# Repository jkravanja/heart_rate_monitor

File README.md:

# heart_rate_monitor
Heart rate monitor designed in KiCad, using Nordic Semiconductor NRF51822 bluetooth module and TI AFE4400 heart rate module.

The repository contains a KiCad design of a 5x5 cm heart rate monitor breakout board. Some libraries were borrowed from Guan Yang's github projects (https://github.com/guanix/boards). Also, some design aspects of the circuit were inspired by HackManhattan Nordic nrf51822 beakout board (http://dangerousprototypes.com/2013/05/19/hackmanhattans-nordic-nrf51822-breakout-board/)

[Schematics](https://github.com/jkravanja/heart_rate_monitor/blob/master/hr.pdf)

In addition to AFE440 for heart rate measurements and NRF51822 for BLE communications, the circuit also contains a [Freescale MMA8452 3-axis accelerometer](http://www.nxp.com/files/sensors/doc/data_sheet/MMA8452Q.pdf), CAT24M01 1Mb EEPROM and an additional heart rate circuit composed of just a few simple elements (see bottom center of the schematics). The circuit was inspired by [this article](http://www.biofotonika.lu.lv/fileadmin/user_upload/lu_portal/projekti/biofotonika/Publikacijas/A4/SPIE/22.Kviesis-A_photoplethysmography_device_for_multipurpose_blood_circulatory_system_assessment.pdf) and presents a cheaper and simpler option to AFE4400.

Image of manufactured PCB

Components were soldered with reflow technique. Some joints had to be manually corrected using soldering iron

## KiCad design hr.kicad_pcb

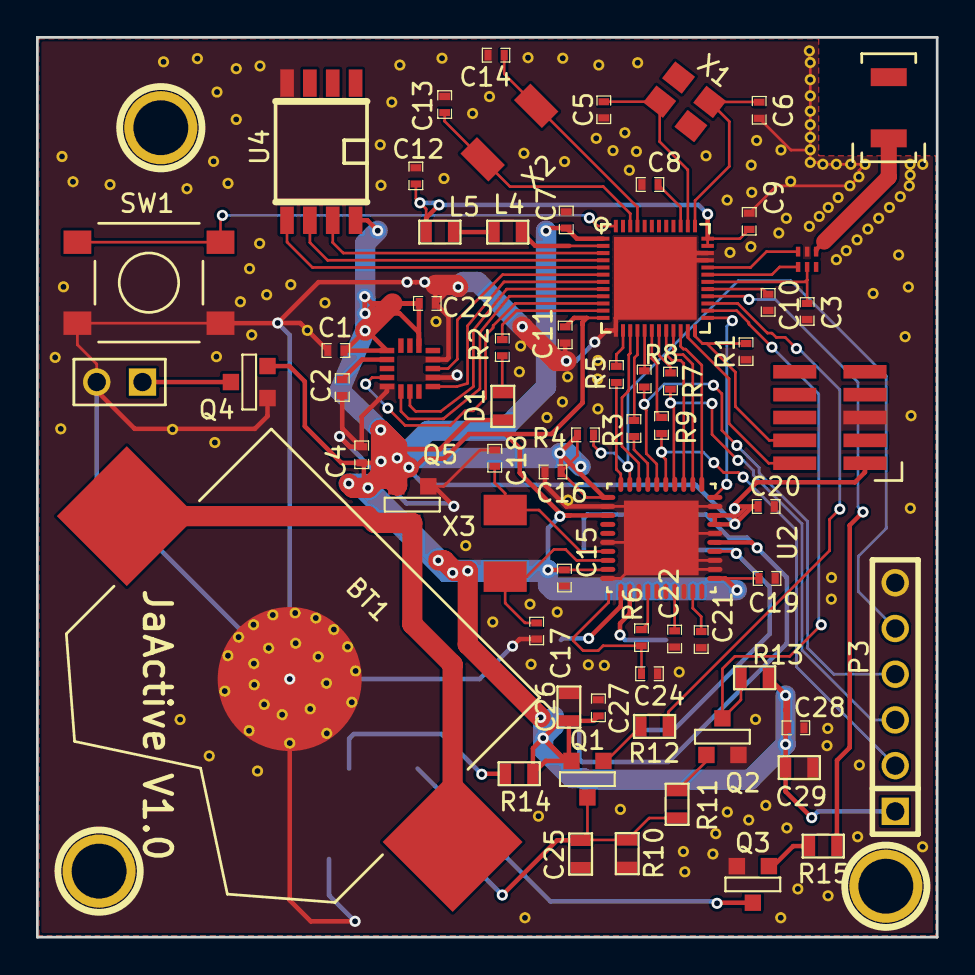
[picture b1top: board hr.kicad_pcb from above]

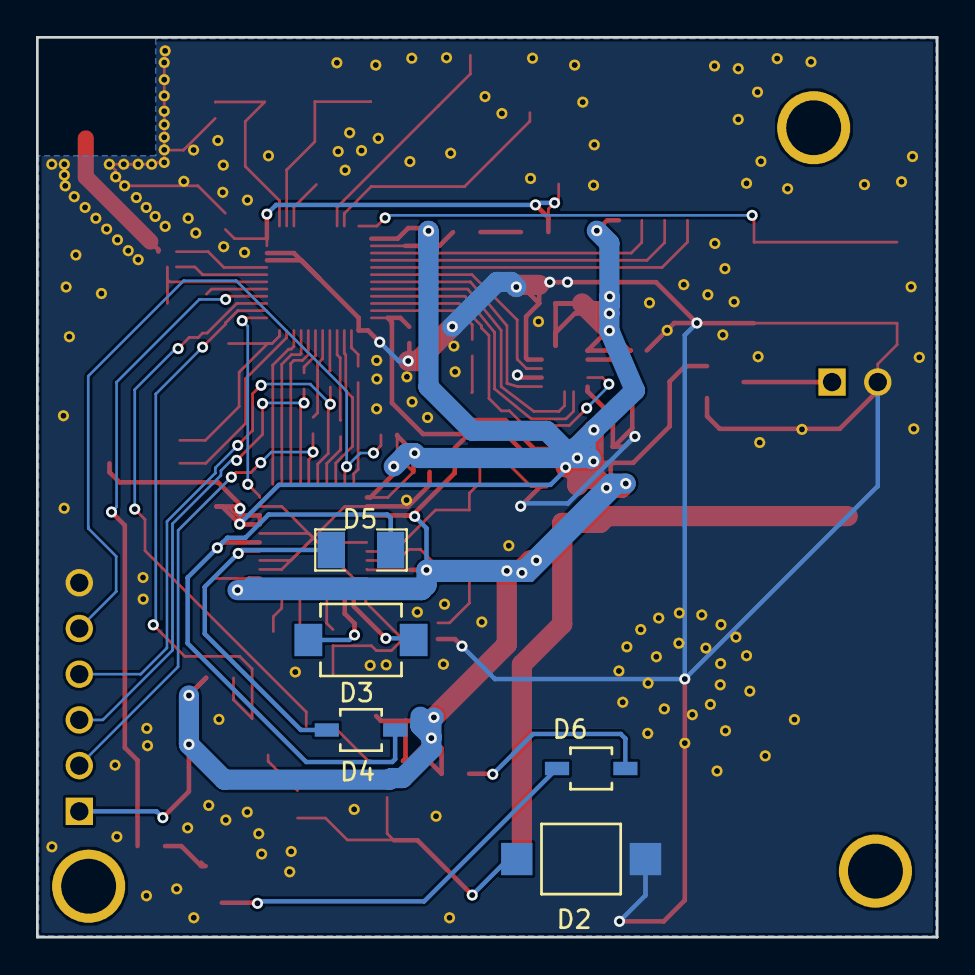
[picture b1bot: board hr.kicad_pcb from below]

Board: 2 copper layers, 50.0 x 50.0 mm, 74 parts (5 on the bottom side), 66 nets.

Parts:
1PIN, 1PIN#2, 1PIN#3: P***; 1pin
B1: Balun Johanson 2450BM14A0002; BALUNJOHANSON-2450BM14A0002
BT1: BATTERY; BatteryHolderCR2032
C1, C2, C16: 0.1 uF; SM0402
C3: 2.2nF; SM0402
C4, C7: 4.7uF; SM0402
C5, C6, C13, C14: 20pF; SM0402
C8, C11, C15, C19: 0.1uF; SM0402
C9: 1nF; SM0402
C10: 47nF; SM0402
C12, C20: 1uF; SM0402
C17, C18: 33p; SM0402
C21, C22: 2.2uF; SM0402
C23: 4.7 uF; SM0402
C24: 0.01 uF; SM0402
C25, C29: 1 nF; SM0603
C26: 220 nF; SM0603
C27, C28: 1 uF; SM0402
D1: LED; SM0603
D2: PHOTODIODE; VBPW34FA
D3: PHOTODIODE; QSB34_Photodiode
D4: IR; VSBM2943
D5: RED; SM1206
D6: LED; VSBM2943
IC1: NRF51822; QFN48+1-0.4MM-SHORTPADS
L4: 10uH; SM0603
L5: 15nH; SM0603
P1: CONN_5X2; PIN-5x2-50MIL
P2: CONN_2; PIN_ARRAY_2X1
P3: CONN_3X2; PIN_ARRAY-6X1
Q1, Q4, Q5: MOSFET_P; SOT23GDS
Q2, Q3: MOSFET_N; SOT23GDS
R1: 12K; SM0402
R2: 100R; SM0402
R3, R7, R8, R9: 4.7k; SM0402
R4: 10k; SM0402
R5: 10; SM0402
R6: 1k; SM0402
R10: 1 M; SM0603
R11, R12: 100 k; SM0603
R13: 3 k; SM0603
R14, R15: R; SM0603
SW1: SWITCH-4; Switch-B3S
U1: ANTENNA Johanson 2450AT18A100E; ANTENNA-JOHANSON-2.45GHZ
U2: AFE4400; QFN40-AFE4400-noVias
U3: MMA8452Q
U4: CAT24M01; SOIC8-5.3MM
X1: 16.000MHZ; 16Mhz_crystal
X2: 32.768 kHz; 32768kHz_Crystal
X3: 8 MHz; 8MHzCrystal

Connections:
/AFE_ADC_RDY: IC1.15, U2.28
/AFE_CLK_OUT: IC1.14, R5.2
/AFE_DIAG_END: IC1.22, U2.21
/AFE_LED_ALM: IC1.21, U2.22
/AFE_PDN: IC1.25, U2.20
/AFE_PD_ALM: IC1.20, U2.23
/AFE_RESET: P3.5, R4.2, U2.29
/AFE_SCLK: P3.3, R7.2, U2.24
/AFE_SPISIMO: P3.4, R8.2, U2.26
/AFE_SPISOMI: P3.2, R9.2, U2.25
/AFE_SPISTE: R3.2, U2.27
/ANT1: B1.4, IC1.31
/ANT2: B1.3, IC1.32
/CHARGE: IC1.27, R12.2
/EE_SCL: IC1.4, U4.6
/EE_SDA: IC1.5, U4.5
/EE_WP: IC1.3, U4.7
/INT1: IC1.6, U3.11
/INT2: IC1.7, U3.9
/LED1: IC1.11, R2.2
/LED_ON: IC1.28, R15.2
/OUT: IC1.26, Q2.D, R13.2
/SA0: IC1.8, U3.7
/SCL: IC1.10, U3.4
/SDA: IC1.9, U3.6
/SW1: IC1.48, SW1.3, SW1.4
/SWCLK: IC1.24, P1.9, R1.1
/SWDIO: IC1.23, P1.10
/VDD_PA: B1.5, C3.1, IC1.30
AVDD: C9.1, C12.1, IC1.35, IC1.36, L5.1
GND: B1.2, BT1.2, C1.2, C2.2, C3.2, C4.2, C5.1, C6.1, C7.2, C8.2, C9.2, C10.2, C11.2, C12.2, C13.1, C14.1, C15.1, C16.2, C17.1, C18.2, C19.2, C20.2, C21.2, C22.2, C23.2, C24.2, C25.2, C26.2, C27.2, C28.2, C29.2, D2.1, IC1.13, IC1.33, IC1.34, IC1.49, P1.3, P2.2, P3.6, Q2.S, Q3.S, Q4.G, Q5.G, R1.2, R10.2, SW1.1, SW1.2, U2.3, U2.8, U2.12, U2.13, U2.16, U2.19, U2.32, U2.36, U2.40, U2.41, U3.5, U3.10, U3.12, U4.4
unnamed: C17.2, U2.38, X3.1
unnamed: C18.1, U2.37, X3.2
unnamed: C8.1, IC1.39
unnamed: D1.2, R2.1
unnamed: B1.1, U1.1
unnamed: C10.1, IC1.29
unnamed: D4.1, D5.2, U2.15
unnamed: D4.2, D5.1, U2.14
unnamed: D3.2, U2.2
unnamed: C22.1, U2.7
unnamed: Q2.G, R11.2
unnamed: R5.1, U2.30
unnamed: D6.1, R14.2
unnamed: D6.2, Q3.D
unnamed: Q3.G, R15.1
unnamed: Q1.G, R12.1
unnamed: IC1.16, R3.1
unnamed: IC1.17, R8.1
unnamed: IC1.18, R9.1
unnamed: IC1.19, R7.1
unnamed: BT1.1, Q5.D
unnamed: P2.1, Q4.D
unnamed: C21.1, U2.9
unnamed: C24.1, R6.1
unnamed: IC1.2, L4.2
unnamed: L4.1, L5.2
unnamed: R6.2, U2.4
unnamed: D3.1, U2.1
unnamed: C25.1, D2.2, Q1.D, R10.1, R11.1
unnamed: C2.1, U3.2
unnamed: C6.2, IC1.37, X1.1
unnamed: C5.2, IC1.38, X1.2
unnamed: C13.2, IC1.46, X2.1
unnamed: C14.2, IC1.45, X2.2
VCC: C1.1, C4.1, C7.1, C11.1, C15.2, C16.1, C19.1, C20.1, C23.1, C26.1, C27.1, C28.1, C29.1, D1.1, IC1.1, IC1.12, P1.1, P3.1, Q1.S, Q4.S, Q5.S, R4.1, R13.1, R14.1, U2.11, U2.17, U2.18, U2.31, U2.33, U2.39, U3.1, U3.14, U4.8

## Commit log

2016-01-17 Initial commit.
2016-01-17 Delete _autosave-.kicad_pcb
    remove _autosave
2016-01-17 Update README.md
    Updated readme
2016-01-17 Added images
2016-01-17 Delete 2.jpeg
    deleted 2.jpeg
